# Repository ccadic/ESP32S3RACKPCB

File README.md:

# ESP32S3RACKPCB
This is a 1U rack PCB to hold 8 x ESP32S3 Wroom chips.

You have the STEP file, solidworks files, Kicad files and gerbers
@sulfuroid

My USDT address: 0xA7Cb711124e1Be5cad35aABB5d8a29b6dfdfc594 for coffees...

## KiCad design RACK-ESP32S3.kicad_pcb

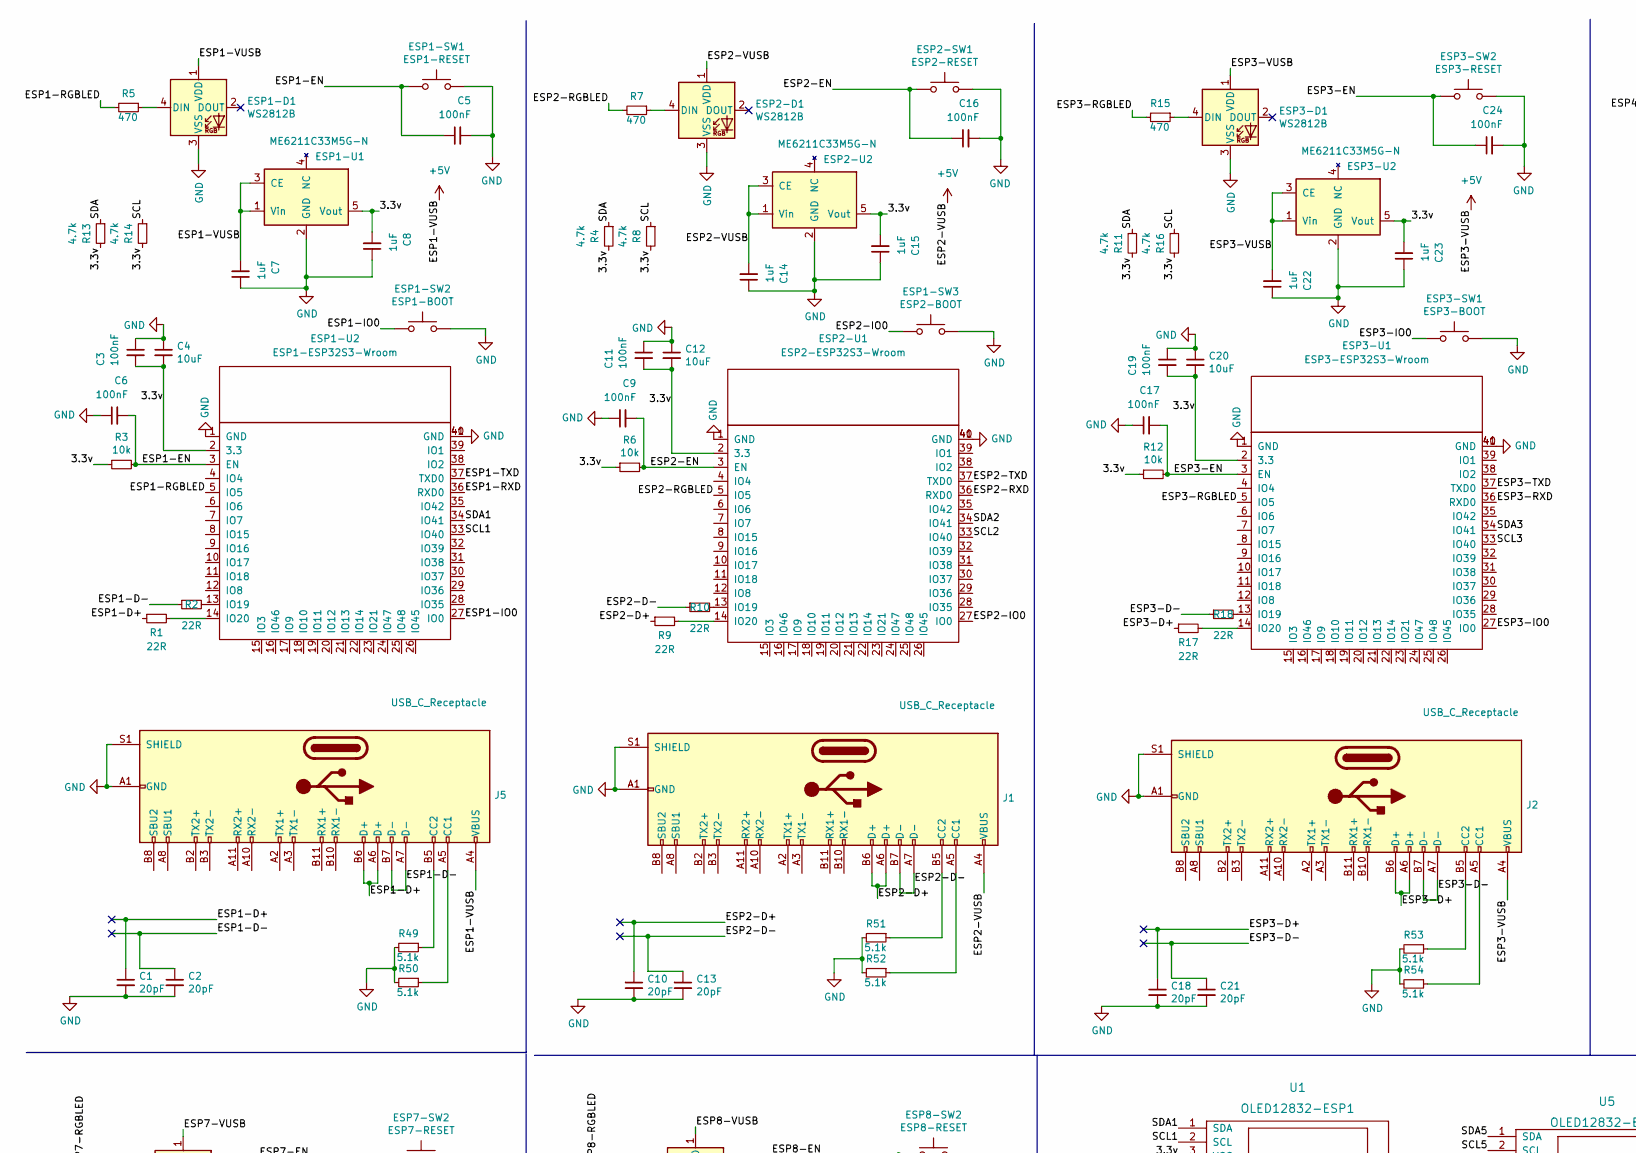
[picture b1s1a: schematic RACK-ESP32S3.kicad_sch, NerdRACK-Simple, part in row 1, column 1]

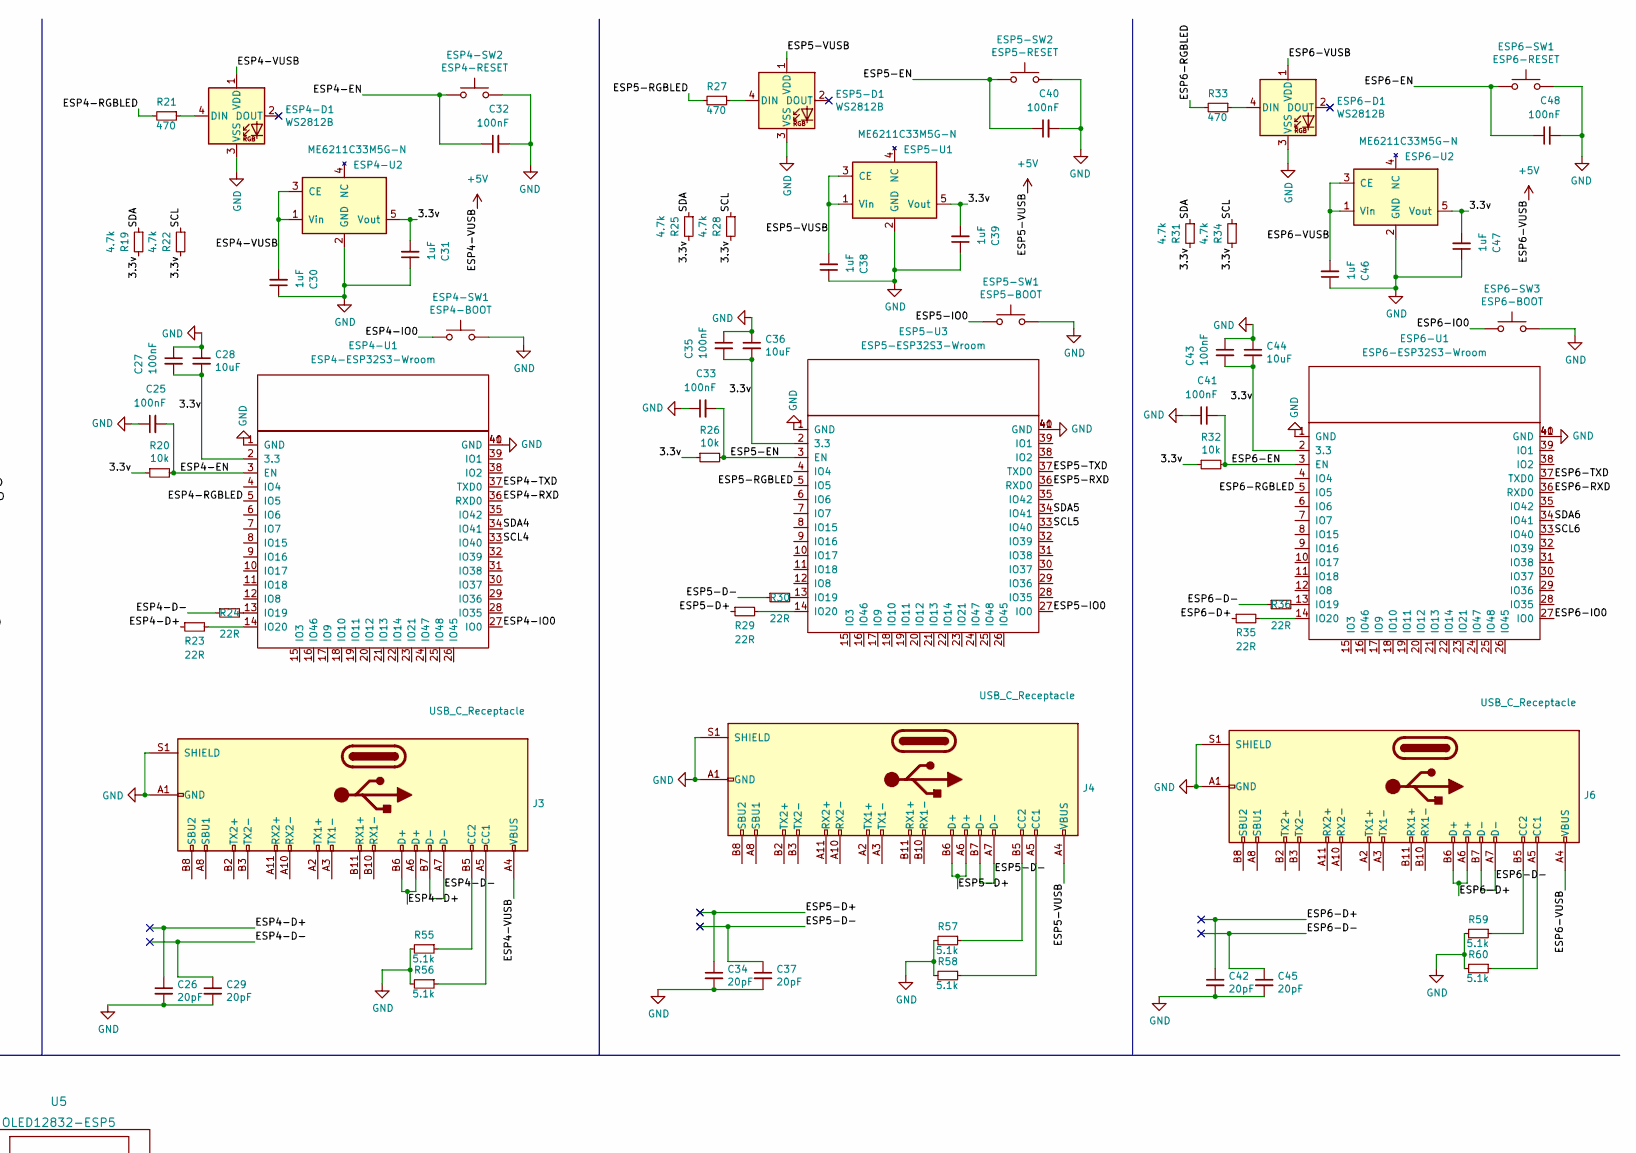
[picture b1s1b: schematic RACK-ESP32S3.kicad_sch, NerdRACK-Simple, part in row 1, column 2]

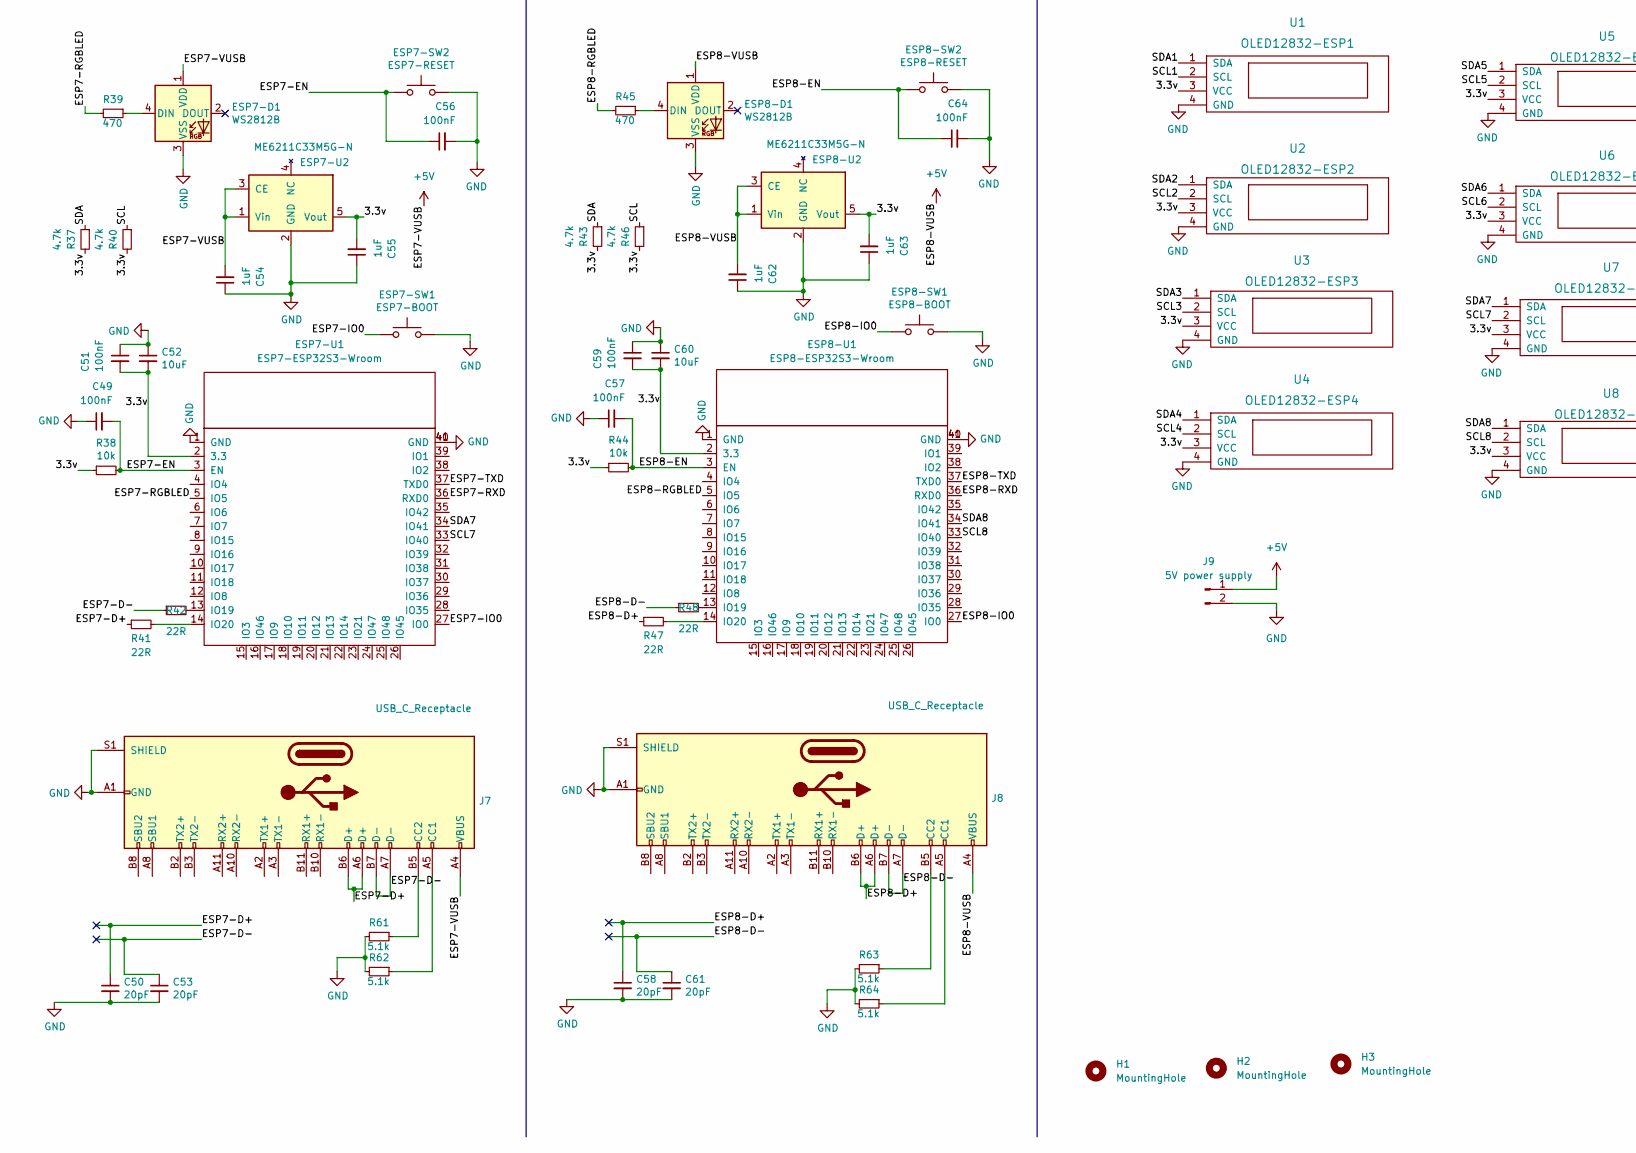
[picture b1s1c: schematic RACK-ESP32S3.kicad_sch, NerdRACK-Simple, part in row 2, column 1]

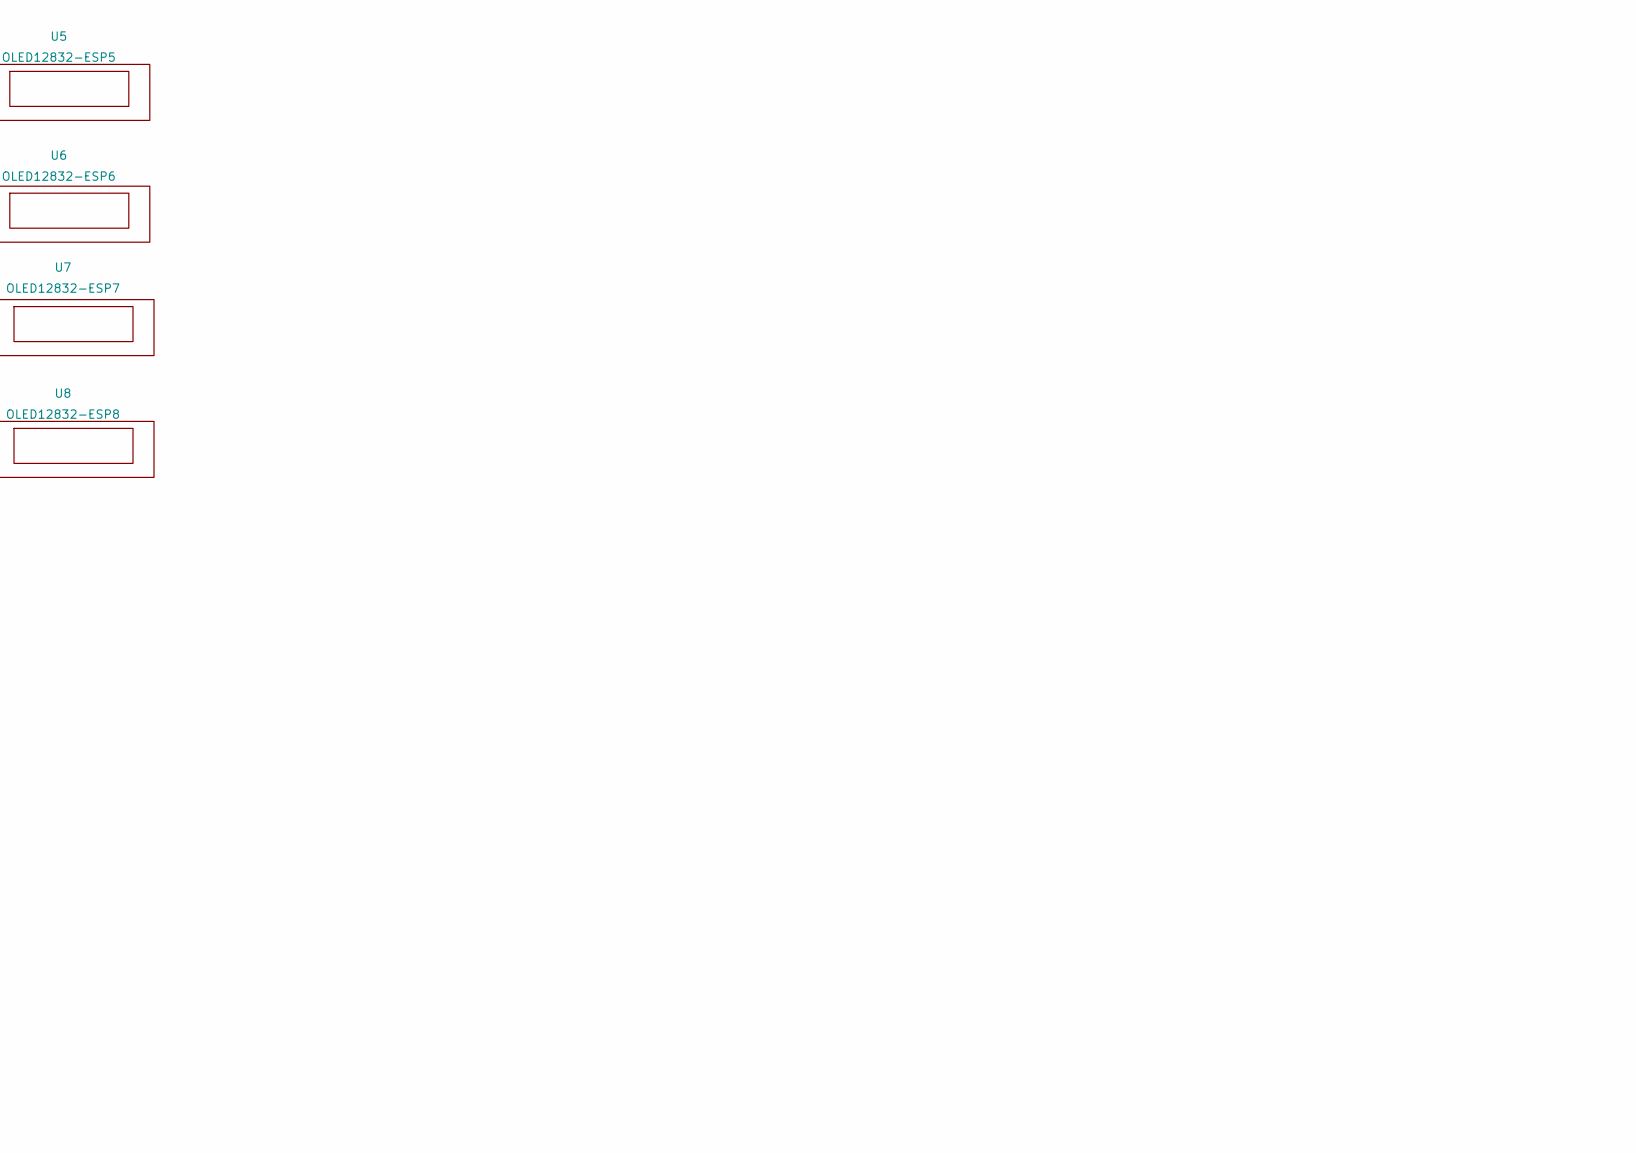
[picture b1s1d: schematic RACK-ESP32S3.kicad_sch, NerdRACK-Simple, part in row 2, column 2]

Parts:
C1, C2, C10, C13, C18, C21, C26, C29, C34, C37, C42, C45, C50, C53, C58, C61: 20pF; C_0603_1608Metric
C3, C5, C6, C9, C11, C16, C17, C19, C24, C25, C27, C32, C33, C35, C40, C41, C43, C48, C49, C51, C56, C57, C59, C64: 100nF; C_0603_1608Metric
C4, C12, C20, C28, C36, C44, C52, C60: 10uF; C_0603_1608Metric
C7, C8, C14, C15, C22, C23, C30, C31, C38, C39, C46, C47, C54, C55, C62, C63: 1uF; C_0603_1608Metric
ESP1-D1, ESP2-D1, ESP3-D1, ESP4-D1, ESP5-D1, ESP6-D1, ESP7-D1, ESP8-D1: WS2812B; LED_WS2812B_PLCC4_5.0x5.0mm_P3.2mm
ESP1-SW1: ESP1-RESET; SW_SPST_B3U-1000P
ESP1-SW2: ESP1-BOOT; SW_SPST_B3U-1000P
ESP1-SW3: ESP2-BOOT; SW_SPST_B3U-1000P
ESP1-U1, ESP2-U2, ESP3-U2, ESP4-U2, ESP5-U1, ESP6-U2, ESP7-U2, ESP8-U2: ME6211C33M5G-N; SOT-23-5
ESP1-U2: ESP1-ESP32S3-Wroom; ESP32-S3-WROOM-1
ESP2-SW1: ESP2-RESET; SW_SPST_B3U-1000P
ESP2-U1: ESP2-ESP32S3-Wroom; ESP32-S3-WROOM-1
ESP3-SW1: ESP3-BOOT; SW_SPST_B3U-1000P
ESP3-SW2: ESP3-RESET; SW_SPST_B3U-1000P
ESP3-U1: ESP3-ESP32S3-Wroom; ESP32-S3-WROOM-1
ESP4-SW1: ESP4-BOOT; SW_SPST_B3U-1000P
ESP4-SW2: ESP4-RESET; SW_SPST_B3U-1000P
ESP4-U1: ESP4-ESP32S3-Wroom; ESP32-S3-WROOM-1
ESP5-SW1: ESP5-BOOT; SW_SPST_B3U-1000P
ESP5-SW2: ESP5-RESET; SW_SPST_B3U-1000P
ESP5-U3: ESP5-ESP32S3-Wroom; ESP32-S3-WROOM-1
ESP6-SW1: ESP6-RESET; SW_SPST_B3U-1000P
ESP6-SW3: ESP6-BOOT; SW_SPST_B3U-1000P
ESP6-U1: ESP6-ESP32S3-Wroom; ESP32-S3-WROOM-1
ESP7-SW1: ESP7-BOOT; SW_SPST_B3U-1000P
ESP7-SW2: ESP7-RESET; SW_SPST_B3U-1000P
ESP7-U1: ESP7-ESP32S3-Wroom; ESP32-S3-WROOM-1
ESP8-SW1: ESP8-BOOT; SW_SPST_B3U-1000P
ESP8-SW2: ESP8-RESET; SW_SPST_B3U-1000P
ESP8-U1: ESP8-ESP32S3-Wroom; ESP32-S3-WROOM-1
H1, H2, H3: MountingHole; MountingHole_3.5mm
J1, J2, J3, J4, J5, J6, J7, J8: USB_C_Receptacle; GT-USB-7010
J9: 5V power supply; TerminalBlock_bornier-2_P5.08mm
R1, R2, R9, R10, R17, R18, R23, R24, R29, R30, R35, R36, R41, R42, R47, R48: 22R; R_0603_1608Metric
R3, R6, R12, R20, R26, R32, R38, R44: 10k; R_0603_1608Metric
R4, R8, R11, R13, R14, R16, R19, R22, R25, R28, R31, R34, R37, R40, R43, R46: 4.7k; R_0603_1608Metric
R5, R7, R15, R21, R27, R33, R39, R45: 470; R_0603_1608Metric
R49, R50, R51, R52, R53, R54, R55, R56, R57, R58, R59, R60, R61, R62, R63, R64: 5.1k; R_0603_1608Metric
U1: OLED12832-ESP1; OLED-0.91-128x32
U2: OLED12832-ESP2; OLED-0.91-128x32
U3: OLED12832-ESP3; OLED-0.91-128x32
U4: OLED12832-ESP4; OLED-0.91-128x32
U5: OLED12832-ESP5; OLED-0.91-128x32
U6: OLED12832-ESP6; OLED-0.91-128x32
U7: OLED12832-ESP7; OLED-0.91-128x32
U8: OLED12832-ESP8; OLED-0.91-128x32

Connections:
+5V: C7.2, C14.2, C22.2, C30.2, C38.2, C46.2, C54.2, C62.2, ESP1-D1.1 (VDD), ESP1-U1.1 (Vin), ESP1-U1.3 (CE), ESP2-D1.1 (VDD), ESP2-U2.1 (Vin), ESP2-U2.3 (CE), ESP3-D1.1 (VDD), ESP3-U2.1 (Vin), ESP3-U2.3 (CE), ESP4-D1.1 (VDD), ESP4-U2.1 (Vin), ESP4-U2.3 (CE), ESP5-D1.1 (VDD), ESP5-U1.1 (Vin), ESP5-U1.3 (CE), ESP6-D1.1 (VDD), ESP6-U2.1 (Vin), ESP6-U2.3 (CE), ESP7-D1.1 (VDD), ESP7-U2.1 (Vin), ESP7-U2.3 (CE), ESP8-D1.1 (VDD), ESP8-U2.1 (Vin), ESP8-U2.3 (CE), J1.A4 (VBUS), J1.A9 (VBUS), J1.B4 (VBUS), J1.B9 (VBUS), J2.A4 (VBUS), J2.A9 (VBUS), J2.B4 (VBUS), J2.B9 (VBUS), J3.A4 (VBUS), J3.A9 (VBUS), J3.B4 (VBUS), J3.B9 (VBUS), J4.A4 (VBUS), J4.A9 (VBUS), J4.B4 (VBUS), J4.B9 (VBUS), J5.A4 (VBUS), J5.A9 (VBUS), J5.B4 (VBUS), J5.B9 (VBUS), J6.A4 (VBUS), J6.A9 (VBUS), J6.B4 (VBUS), J6.B9 (VBUS), J7.A4 (VBUS), J7.A9 (VBUS), J7.B4 (VBUS), J7.B9 (VBUS), J8.A4 (VBUS), J8.A9 (VBUS), J8.B4 (VBUS), J8.B9 (VBUS), J9.1
/3.3v: C3.2, C4.2, C8.2, C11.2, C12.2, C15.2, C19.2, C20.2, C23.2, C27.2, C28.2, C31.2, C35.2, C36.2, C39.2, C43.2, C44.2, C47.2, C51.2, C52.2, C55.2, C59.2, C60.2, C63.2, ESP1-U1.5 (Vout), ESP1-U2.2 (3.3), ESP2-U1.2 (3.3), ESP2-U2.5 (Vout), ESP3-U1.2 (3.3), ESP3-U2.5 (Vout), ESP4-U1.2 (3.3), ESP4-U2.5 (Vout), ESP5-U1.5 (Vout), ESP5-U3.2 (3.3), ESP6-U1.2 (3.3), ESP6-U2.5 (Vout), ESP7-U1.2 (3.3), ESP7-U2.5 (Vout), ESP8-U1.2 (3.3), ESP8-U2.5 (Vout), R3.1, R4.2, R6.1, R8.2, R11.2, R12.1, R13.2, R14.2, R16.2, R19.2, R20.1, R22.2, R25.2, R26.1, R28.2, R31.2, R32.1, R34.2, R37.2, R38.1, R40.2, R43.2, R44.1, R46.2, U1.3 (VCC), U2.3 (VCC), U3.3 (VCC), U4.3 (VCC), U5.3 (VCC), U6.3 (VCC), U7.3 (VCC), U8.3 (VCC); also elsewhere on the board
/ESP1-D+: C1.1, J5.A6 (D+), J5.B6 (D+), R1.1
/ESP1-D-: C2.1, J5.A7 (D-), J5.B7 (D-), R2.1
/ESP1-EN: C5.1, C6.2, ESP1-SW1.2, ESP1-U2.3 (EN), R3.2
/ESP1-IO0: ESP1-SW2.1, ESP1-U2.27 (IO0)
/ESP1-RGBLED: ESP1-U2.5 (IO5), R5.2
/ESP1-RXD: ESP1-U2.36 (RXD0)
/ESP1-TXD: ESP1-U2.37 (TXD0)
/ESP2-D+: C10.1, J1.A6 (D+), J1.B6 (D+), R9.1
/ESP2-D-: C13.1, J1.A7 (D-), J1.B7 (D-), R10.1
/ESP2-EN: C9.2, C16.1, ESP2-SW1.2, ESP2-U1.3 (EN), R6.2
/ESP2-IO0: ESP1-SW3.1, ESP2-U1.27 (IO0)
/ESP2-RGBLED: ESP2-U1.5 (IO5), R7.2
/ESP2-RXD: ESP2-U1.36 (RXD0)
/ESP2-TXD: ESP2-U1.37 (TXD0)
/ESP3-D+: C18.1, J2.A6 (D+), J2.B6 (D+), R17.1
/ESP3-D-: C21.1, J2.A7 (D-), J2.B7 (D-), R18.1
/ESP3-EN: C17.2, C24.1, ESP3-SW2.2, ESP3-U1.3 (EN), R12.2
/ESP3-IO0: ESP3-SW1.1, ESP3-U1.27 (IO0)
/ESP3-RGBLED: ESP3-U1.5 (IO5), R15.2
/ESP3-RXD: ESP3-U1.36 (RXD0)
/ESP3-TXD: ESP3-U1.37 (TXD0)
/ESP4-D+: C26.1, J3.A6 (D+), J3.B6 (D+), R23.1
/ESP4-D-: C29.1, J3.A7 (D-), J3.B7 (D-), R24.1
/ESP4-EN: C25.2, C32.1, ESP4-SW2.2, ESP4-U1.3 (EN), R20.2
/ESP4-IO0: ESP4-SW1.1, ESP4-U1.27 (IO0)
/ESP4-RGBLED: ESP4-U1.5 (IO5), R21.2
/ESP4-RXD: ESP4-U1.36 (RXD0)
/ESP4-TXD: ESP4-U1.37 (TXD0)
/ESP5-D+: C34.1, J4.A6 (D+), J4.B6 (D+), R29.1
/ESP5-D-: C37.1, J4.A7 (D-), J4.B7 (D-), R30.1
/ESP5-EN: C33.2, C40.1, ESP5-SW2.2, ESP5-U3.3 (EN), R26.2
/ESP5-IO0: ESP5-SW1.1, ESP5-U3.27 (IO0)
/ESP5-RGBLED: ESP5-U3.5 (IO5), R27.2
/ESP5-RXD: ESP5-U3.36 (RXD0)
/ESP5-TXD: ESP5-U3.37 (TXD0)
/ESP6-D+: C42.1, J6.A6 (D+), J6.B6 (D+), R35.1
/ESP6-D-: C45.1, J6.A7 (D-), J6.B7 (D-), R36.1
/ESP6-EN: C41.2, C48.1, ESP6-SW1.2, ESP6-U1.3 (EN), R32.2; also elsewhere on the board
/ESP6-IO0: ESP6-SW3.1, ESP6-U1.27 (IO0); also elsewhere on the board
/ESP6-RGBLED: ESP6-U1.5 (IO5), R33.2; also elsewhere on the board
/ESP7-D+: C50.1, J7.A6 (D+), J7.B6 (D+), R41.1
/ESP7-D-: C53.1, J7.A7 (D-), J7.B7 (D-), R42.1
/ESP7-EN: C49.2, C56.1, ESP7-SW2.2, ESP7-U1.3 (EN), R38.2
/ESP7-IO0: ESP7-SW1.1, ESP7-U1.27 (IO0)
/ESP7-RGBLED: ESP7-U1.5 (IO5), R39.2
/ESP7-RXD: ESP7-U1.36 (RXD0)
/ESP7-TXD: ESP7-U1.37 (TXD0)
/ESP8-D+: C58.1, J8.A6 (D+), J8.B6 (D+), R47.1
/ESP8-D-: C61.1, J8.A7 (D-), J8.B7 (D-), R48.1
/ESP8-EN: C57.2, C64.1, ESP8-SW2.2, ESP8-U1.3 (EN), R44.2
/ESP8-IO0: ESP8-SW1.1, ESP8-U1.27 (IO0)
/ESP8-RGBLED: ESP8-U1.5 (IO5), R45.2
/ESP8-RXD: ESP8-U1.36 (RXD0)
/ESP8-TXD: ESP8-U1.37 (TXD0)
/SCL: R8.1, R14.1, R16.1, R22.1, R28.1, R34.1, R40.1, R46.1
/SCL1: ESP1-U2.33 (IO40), U1.2 (SCL)
/SCL2: ESP2-U1.33 (IO40), U2.2 (SCL)
/SCL3: ESP3-U1.33 (IO40), U3.2 (SCL)
/SCL4: ESP4-U1.33 (IO40), U4.2 (SCL)
/SCL5: ESP5-U3.33 (IO40), U5.2 (SCL)
/SCL6: ESP6-U1.33 (IO40), U6.2 (SCL); also elsewhere on the board
/SCL7: ESP7-U1.33 (IO40), U7.2 (SCL)
/SCL8: ESP8-U1.33 (IO40), U8.2 (SCL)
/SDA: R4.1, R11.1, R13.1, R19.1, R25.1, R31.1, R37.1, R43.1
/SDA1: ESP1-U2.34 (IO41), U1.1 (SDA)
/SDA2: ESP2-U1.34 (IO41), U2.1 (SDA)
/SDA3: ESP3-U1.34 (IO41), U3.1 (SDA)
/SDA4: ESP4-U1.34 (IO41), U4.1 (SDA)
/SDA5: ESP5-U3.34 (IO41), U5.1 (SDA)
/SDA6: ESP6-U1.34 (IO41), U6.1 (SDA); also elsewhere on the board
/SDA7: ESP7-U1.34 (IO41), U7.1 (SDA)
/SDA8: ESP8-U1.34 (IO41), U8.1 (SDA)
GND: C1.2, C2.2, C3.1, C4.1, C5.2, C6.1, C7.1, C8.1, C9.1, C10.2, C11.1, C12.1, C13.2, C14.1, C15.1, C16.2, C17.1, C18.2, C19.1, C20.1, C21.2, C22.1, C23.1, C24.2, C25.1, C26.2, C27.1, C28.1, C29.2, C30.1, C31.1, C32.2, C33.1, C34.2, C35.1, C36.1, C37.2, C38.1, C39.1, C40.2, C41.1, C42.2, C43.1, C44.1, C45.2, C46.1, C47.1, C48.2, C49.1, C50.2, C51.1, C52.1, C53.2, C54.1, C55.1, C56.2, C57.1, C58.2, C59.1, C60.1, C61.2, C62.1, C63.1, C64.2, ESP1-D1.3 (VSS), ESP1-SW1.1, ESP1-SW2.2, ESP1-SW3.2, ESP1-U1.2 (GND), ESP1-U2.1 (GND), ESP1-U2.40 (GND), ESP1-U2.41 (GND), ESP2-D1.3 (VSS), ESP2-SW1.1, ESP2-U1.1 (GND), ESP2-U1.40 (GND), ESP2-U1.41 (GND), ESP2-U2.2 (GND), ESP3-D1.3 (VSS), ESP3-SW1.2, ESP3-SW2.1, ESP3-U1.1 (GND), ESP3-U1.40 (GND), ESP3-U1.41 (GND), ESP3-U2.2 (GND), ESP4-D1.3 (VSS), ESP4-SW1.2, ESP4-SW2.1, ESP4-U1.1 (GND), ESP4-U1.40 (GND), ESP4-U1.41 (GND), ESP4-U2.2 (GND), ESP5-D1.3 (VSS), ESP5-SW1.2, ESP5-SW2.1, ESP5-U1.2 (GND), ESP5-U3.1 (GND), ESP5-U3.40 (GND), ESP5-U3.41 (GND), ESP6-D1.3 (VSS), ESP6-SW1.1, ESP6-SW3.2, ESP6-U1.1 (GND), ESP6-U1.40 (GND), ESP6-U1.41 (GND), ESP6-U2.2 (GND), ESP7-D1.3 (VSS), ESP7-SW1.2, ESP7-SW2.1, ESP7-U1.1 (GND), ESP7-U1.40 (GND), ESP7-U1.41 (GND), ESP7-U2.2 (GND), ESP8-D1.3 (VSS), ESP8-SW1.2, ESP8-SW2.1, ESP8-U1.1 (GND), ESP8-U1.40 (GND), ESP8-U1.41 (GND), ESP8-U2.2 (GND), J1.A1 (GND), J1.A12 (GND), J1.B1 (GND), J1.B12 (GND), J1.S1 (SHIELD), J2.A1 (GND), J2.A12 (GND), J2.B1 (GND), J2.B12 (GND), J2.S1 (SHIELD), J3.A1 (GND), J3.A12 (GND), J3.B1 (GND), J3.B12 (GND), J3.S1 (SHIELD), J4.A1 (GND), J4.A12 (GND), J4.B1 (GND), J4.B12 (GND), J4.S1 (SHIELD), J5.A1 (GND), J5.A12 (GND), J5.B1 (GND), J5.B12 (GND), J5.S1 (SHIELD), J6.A1 (GND), J6.A12 (GND), J6.B1 (GND), J6.B12 (GND), J6.S1 (SHIELD), J7.A1 (GND), J7.A12 (GND), J7.B1 (GND), J7.B12 (GND), J7.S1 (SHIELD), J8.A1 (GND), J8.A12 (GND), J8.B1 (GND), J8.B12 (GND), J8.S1 (SHIELD), J9.2, R49.2, R50.2, R51.2, R52.2, R53.2, R54.2, R55.2, R56.2, R57.2, R58.2, R59.2, R60.2, R61.2, R62.2, R63.2, R64.2, U1.4 (GND), U2.4 (GND), U3.4 (GND), U4.4 (GND), U5.4 (GND), U6.4 (GND), U7.4 (GND), U8.4 (GND); also elsewhere on the board
unnamed: ESP1-D1.4 (DIN), R5.1
unnamed: ESP1-U2.13 (IO19), R2.2
unnamed: ESP1-U2.14 (IO20), R1.2
unnamed: ESP2-D1.4 (DIN), R7.1
unnamed: ESP2-U1.13 (IO19), R10.2
unnamed: ESP2-U1.14 (IO20), R9.2
unnamed: ESP3-D1.4 (DIN), R15.1
unnamed: ESP3-U1.13 (IO19), R18.2
unnamed: ESP3-U1.14 (IO20), R17.2
unnamed: ESP4-D1.4 (DIN), R21.1
unnamed: ESP4-U1.13 (IO19), R24.2
unnamed: ESP4-U1.14 (IO20), R23.2
unnamed: ESP5-D1.4 (DIN), R27.1
unnamed: ESP5-U3.13 (IO19), R30.2
unnamed: ESP5-U3.14 (IO20), R29.2
unnamed: ESP6-D1.4 (DIN), R33.1
unnamed 93: ESP6-U1.13 (IO19), R36.2; also elsewhere on the board
unnamed 94: ESP6-U1.14 (IO20), R35.2; also elsewhere on the board
unnamed: ESP7-D1.4 (DIN), R39.1
unnamed: ESP7-U1.13 (IO19), R42.2
unnamed: ESP7-U1.14 (IO20), R41.2
unnamed: ESP8-D1.4 (DIN), R45.1
unnamed: ESP8-U1.13 (IO19), R48.2
unnamed: ESP8-U1.14 (IO20), R47.2
unnamed: J1.A5 (CC1), R52.1
unnamed: J1.B5 (CC2), R51.1
unnamed: J2.A5 (CC1), R54.1
unnamed: J2.B5 (CC2), R53.1
unnamed: J3.A5 (CC1), R56.1
unnamed: J3.B5 (CC2), R55.1
unnamed: J4.A5 (CC1), R58.1
unnamed: J4.B5 (CC2), R57.1
unnamed: J5.A5 (CC1), R50.1
unnamed: J5.B5 (CC2), R49.1
unnamed: J6.A5 (CC1), R60.1
unnamed: J6.B5 (CC2), R59.1
unnamed: J7.A5 (CC1), R62.1
unnamed: J7.B5 (CC2), R61.1
unnamed: J8.A5 (CC1), R64.1
unnamed: J8.B5 (CC2), R63.1

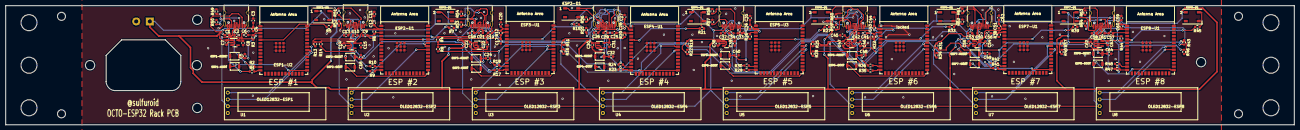
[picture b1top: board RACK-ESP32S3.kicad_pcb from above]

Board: 2 copper layers, 482.6 x 44.6 mm, 188 parts (1 on the bottom side), 101 nets.

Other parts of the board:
locked: ESP6-ESP32S3-Wroom; ESP32-S3-WROOM-1

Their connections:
/3.3v: locked.2 (3.3); also elsewhere on the board
/ESP6-EN: locked.3 (EN); also elsewhere on the board
/ESP6-IO0: locked.27 (IO0); also elsewhere on the board
/ESP6-RGBLED: locked.5 (IO5); also elsewhere on the board
/SCL6: locked.33 (IO40); also elsewhere on the board
/SDA6: locked.34 (IO41); also elsewhere on the board
GND: locked.1 (GND), locked.40 (GND), locked.41 (GND); also elsewhere on the board
unnamed 93: locked.13 (IO19); also elsewhere on the board
unnamed 94: locked.14 (IO20); also elsewhere on the board
